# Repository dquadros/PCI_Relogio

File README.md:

# PCI_Relogio
Projeto de hardware e software para um kit de relógio / temporizador / capacímetro

* CapPCI - software para implementar o capacímetro
* Placa - projeto da placa no Kicad
* RelogioPCI - software para implemlementar o relógio
* TestePlacaCap - software para teste da placa

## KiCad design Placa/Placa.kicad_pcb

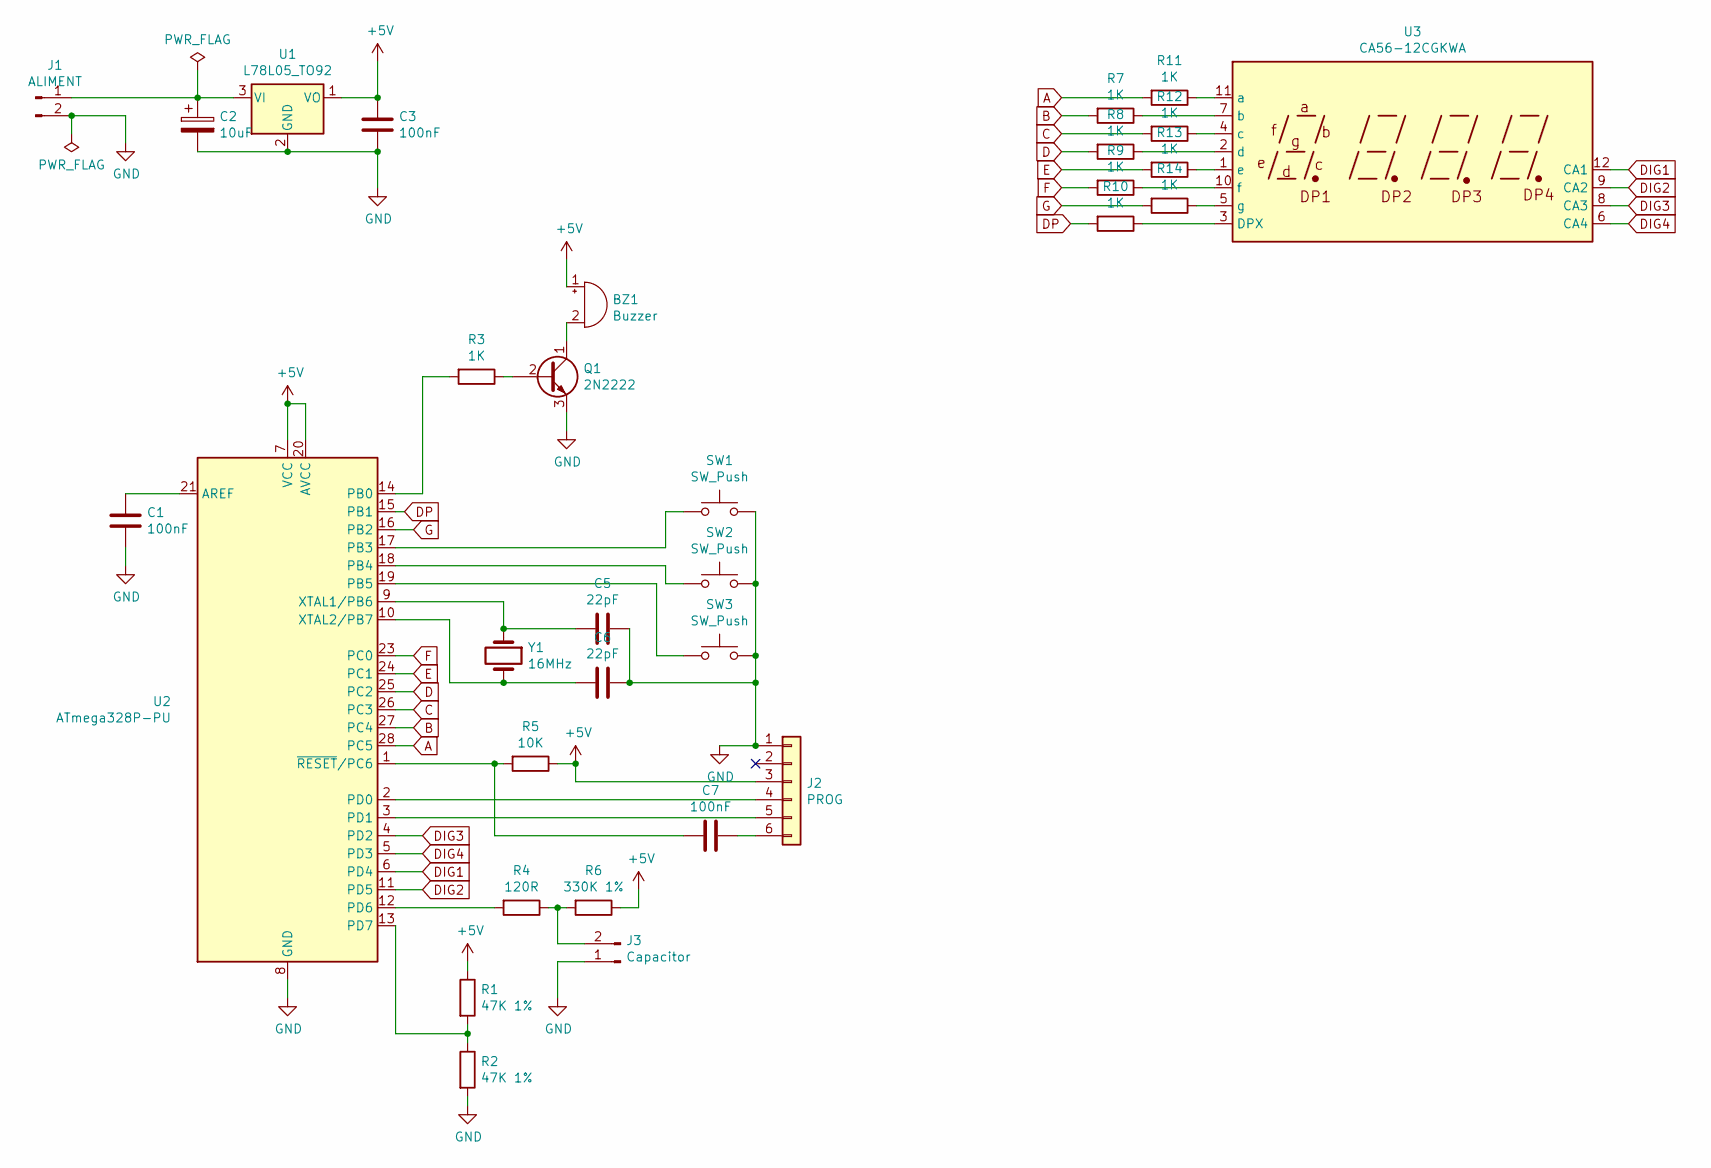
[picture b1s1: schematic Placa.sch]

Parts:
BZ1: Buzzer; Buzzer_12x9.5RM7.6
C1, C3, C7: 100nF; C_Disc_D3.0mm_W2.0mm_P2.50mm
C2: 10uF; C_Radial_D5.0mm_H5.0mm_P2.00mm
C5, C6: 22pF; C_Disc_D3.0mm_W2.0mm_P2.50mm
J1: ALIMENT; PinHeader_1x02_P2.54mm_Vertical
J2: PROG; PinHeader_1x06_P2.54mm_Vertical
J3: Capacitor; PinHeader_1x02_P2.54mm_Vertical
Q1: 2N2222; TO-92
R1, R2: 47K 1%; R_Axial_DIN0207_L6.3mm_D2.5mm_P10.16mm_Horizontal
R3, R7, R8, R9, R10, R11, R12, R13, R14: 1K; R_Axial_DIN0207_L6.3mm_D2.5mm_P10.16mm_Horizontal
R4: 120R; R_Axial_DIN0207_L6.3mm_D2.5mm_P10.16mm_Horizontal
R5: 10K; R_Axial_DIN0207_L6.3mm_D2.5mm_P10.16mm_Horizontal
R6: 330K 1%; R_Axial_DIN0207_L6.3mm_D2.5mm_P10.16mm_Horizontal
SW1, SW2, SW3: SW_Push; SW_PUSH_6mm_H5mm
U1: L78L05_TO92; TO-92_Inline
U2: ATmega328P-PU; DIP-28_W7.62mm
U3: CA56-12CGKWA
Y1: 16MHz; Crystal_HC49-U_Vertical

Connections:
+5V: BZ1.1 (-), C3.1, J2.3, R1.1, R5.1, R6.1, U1.1 (VO), U2.7 (VCC), U2.20 (AVCC)
A: R11.2, U2.28 (PC5)
B: R7.2, U2.27 (PC4)
C: R12.2, U2.26 (PC3)
D: R8.2, U2.25 (PC2)
DIG1: U2.6 (PD4), U3.12 (CA1)
DIG2: U2.11 (PD5), U3.9 (CA2)
DIG3: U2.4 (PD2), U3.8 (CA3)
DIG4: U2.5 (PD3), U3.6 (CA4)
DP: R10.2, U2.15 (PB1)
E: R13.2, U2.24 (PC1)
F: R9.2, U2.23 (PC0)
G: R14.2, U2.16 (PB2)
GND: C1.2, C2.2, C3.2, C5.1, C6.1, J1.2, J2.1, J3.1, Q1.3 (E), R2.2, SW1.2, SW2.2, SW3.2, U1.2 (GND), U2.8 (GND), U2.22 (GND)
unnamed: BZ1.2 (+), Q1.1 (C)
unnamed: C1.1, U2.21 (AREF)
unnamed: C2.1, J1.1, U1.3 (VI)
unnamed: C5.2, U2.9 (XTAL1/PB6), Y1.1
unnamed: C6.2, U2.10 (XTAL2/PB7), Y1.2
unnamed: C7.1, J2.6
unnamed: C7.2, R5.2, U2.1 (~RESET~/PC6)
unnamed: J2.4, U2.2 (PD0)
unnamed: J2.5, U2.3 (PD1)
unnamed: J3.2, R4.1, R6.2
unnamed: Q1.2 (B), R3.1
unnamed: R1.2, R2.1, U2.13 (PD7)
unnamed: R3.2, U2.14 (PB0)
unnamed: R4.2, U2.12 (PD6)
unnamed: R7.1, U3.7 (b)
unnamed: R8.1, U3.2 (d)
unnamed: R9.1, U3.10 (f)
unnamed: R10.1, U3.3 (DPX)
unnamed: R11.1, U3.11 (a)
unnamed: R12.1, U3.4 (c)
unnamed: R13.1, U3.1 (e)
unnamed: R14.1, U3.5 (g)
unnamed: SW1.1, U2.17 (PB3)
unnamed: SW2.1, U2.18 (PB4)
unnamed: SW3.1, U2.19 (PB5)

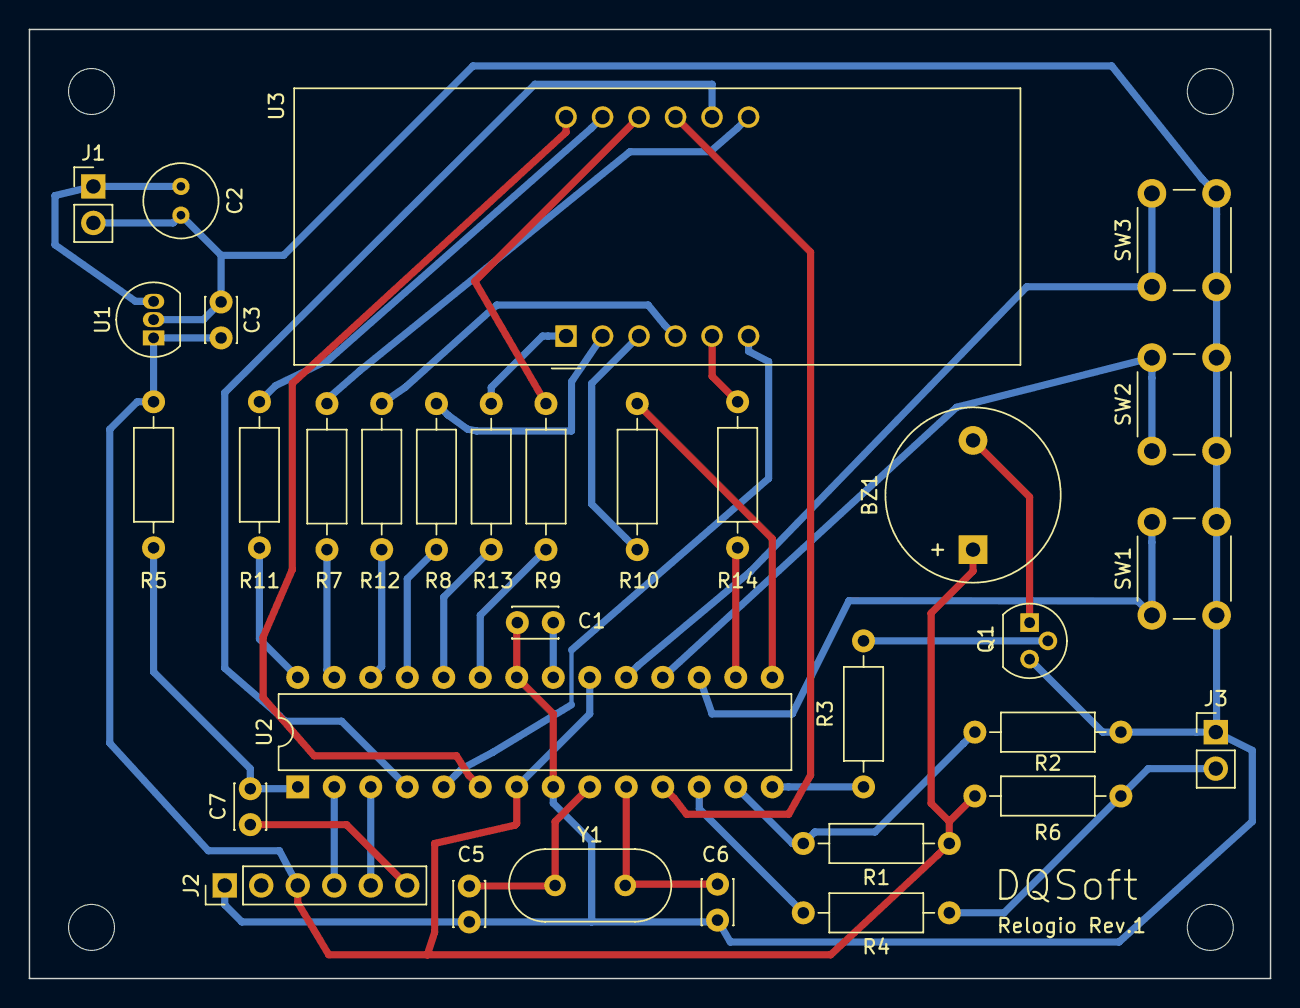
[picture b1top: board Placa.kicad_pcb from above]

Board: 2 copper layers, 86.4 x 66.0 mm, 32 parts (0 on the bottom side), 39 nets.

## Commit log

2019-08-27 Versao inicial
2019-08-28 Acrescentado programa de teste
2020-09-25 Incluido software para relogio
